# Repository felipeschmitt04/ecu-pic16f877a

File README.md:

# ECU with PIC16F877A

Academic embedded systems project developed for a **Microprocessors and
Microcontrollers** course in the Computer Engineering program at UFSC. The goal
was to build an educational ECU prototype that simulates basic combustion engine
control while integrating embedded firmware, sensor acquisition, actuator
control, an LCD interface, circuit simulation, and PCB design.

> **Disclaimer:** this project is intended for academic and portfolio purposes.
> It has not been validated for real automotive use and must not be used to
> control an actual engine without proper electrical, mechanical, and safety
> reviews.

## Overview

The ECU firmware was written in C for the **PIC16F877A** microcontroller using
MPLAB X and the XC8 compiler. The system reads simulated analog sensors, applies
fuel injection maps, controls injectors, ignition outputs, auxiliary actuators,
and displays runtime data on a 16x2 LCD.

The project includes:

- Proteus circuit simulation;
- KiCad schematic and PCB design;
- economy and performance injection maps;
- active map persistence using internal EEPROM;
- button-based user interface with LCD feedback;
- timer and interrupt-driven control logic.

## Visual Documentation

The repository includes exported hardware views that document the path from the
electrical design to the final PCB layout.

The schematic centers on the PIC16F877A and shows the simulated sensor inputs,
LCD interface, user buttons, power connections, and MOSFET-based output stages
used to represent injectors, ignition pairs, the fuel pump, radiator fan,
starter motor, and warning indicators.

The PCB layout shows the two-layer board routing, with the LCD and user controls
placed on the front side and the sensor/actuator connectors distributed around
the board edges for easier access during testing.

| Front side | Back side |
| --- | --- |
|  |  |

The 3D renders highlight the intended physical organization of the prototype:
LCD and buttons on the user-facing side, and the microcontroller, connectors,
crystal oscillator, potentiometer, and driver stages on the opposite side.

## Features

- ADC reading for simulated sensors:
  - TPS;
  - RPM;
  - lambda/oxygen sensor;
  - temperature.
- Two injection maps:
  - economy;
  - performance.
- Sequential injector control.
- Paired ignition output control.
- Auxiliary actuator control:
  - fuel pump;
  - radiator fan;
  - starter motor;
  - check engine LED.
- Simulated open-loop and closed-loop modes.
- RPM limiter.
- Start enrichment logic.
- Multi-screen 16x2 LCD interface.

## How the ECU Works

The firmware runs a simple ECU control loop around four simulated analog
signals: throttle position, RPM, lambda/oxygen feedback, and temperature. Each
loop iteration reads the sensors through the PIC ADC, updates the engine state,
selects a fuel value from a 16x16 lookup table, applies correction rules, and
updates the auxiliary actuators and LCD.

The fuel maps use RPM and TPS as axes. The 10-bit ADC readings are compressed
to 4-bit indexes, producing 16 RPM bands and 16 throttle bands:

```c
rpm_index = adc_rpm >> 6;
tps_index = adc_tps >> 6;
map_index = rpm_index * 16 + tps_index;
```

Two maps are available: an economy map with lower base injection values and a
performance map with richer values. The selected map is stored in internal
EEPROM so the ECU can restore it after a reset.

Timer1 schedules the engine events according to the simulated RPM. On each
Timer1 interrupt, the firmware advances a four-step engine sequence, triggers
one ignition pair, and opens one injector. Timer2 then controls the injector
pulse width and turns all injectors off when the pulse ends.

For a deeper breakdown of the sensors, maps, correction logic, and actuator
states, see [ECU operation](docs/ecu-operation.md).

## Architecture

```mermaid
flowchart LR
    A["Simulated sensors<br/>TPS, RPM, lambda, temperature"] --> B["PIC16F877A ADC"]
    B --> C["ECU logic<br/>maps, corrections, limits"]
    C --> D["Timers and interrupts"]
    D --> E["Injectors"]
    D --> F["Ignition outputs"]
    C --> G["Auxiliary actuators<br/>pump, fan, starter"]
    C --> H["16x2 LCD"]
    I["Buttons"] --> C
    C --> J["Internal EEPROM<br/>active map"]
```

## Project Structure

```text
.
├── Software-MPLab/
│   └── ecu_final.X/        # C firmware for MPLAB X / XC8
├── Hardware-Proteus/       # Circuit simulation
├── PCB-Kicad/
│   └── ecu/                # Schematic and PCB files
└── docs/                   # Technical notes and portfolio assets
```

## Technologies

- **Language:** C
- **Microcontroller:** PIC16F877A
- **IDE/Compiler:** MPLAB X + XC8
- **Simulation:** Proteus
- **PCB Design:** KiCad
- **Interface:** 16x2 LCD in 4-bit mode

## How to Open

### Firmware

1. Open `Software-MPLab/ecu_final.X` in MPLAB X.
2. Confirm that the selected device is `PIC16F877A`.
3. Build the project with the XC8 compiler.

### Simulation

1. Open `Hardware-Proteus/ecu3.pdsprj` in Proteus.
2. Attach the `.hex` file generated by MPLAB to the simulated microcontroller,
   if required.
3. Run the simulation and vary the sensor inputs to observe the ECU behavior.

### PCB

1. Open `PCB-Kicad/ecu/ecu.kicad_pro` in KiCad.
2. Review the schematic and PCB layout.
3. Run ERC/DRC before considering any manufacturing step.

## Known Limitations

This project was developed as an academic prototype. Before any use beyond
simulation, the following areas would need additional work:

- validate the electrical sizing of inductive load drivers;
- replace floating-point calculations with integer or fixed-point arithmetic to
  reduce program memory usage;
- protect variables shared between `main` and interrupt routines;
- review LCD buffers and string formatting;
- make the build reproducible outside the original MPLAB/XC8 environment;
- run and document KiCad ERC/DRC results.

## Outcome

The project was presented for the Microprocessors and Microcontrollers course
and received the maximum grade. It demonstrates practical integration between
embedded firmware, analog/digital electronics, real-time control, circuit
simulation, and PCB design.

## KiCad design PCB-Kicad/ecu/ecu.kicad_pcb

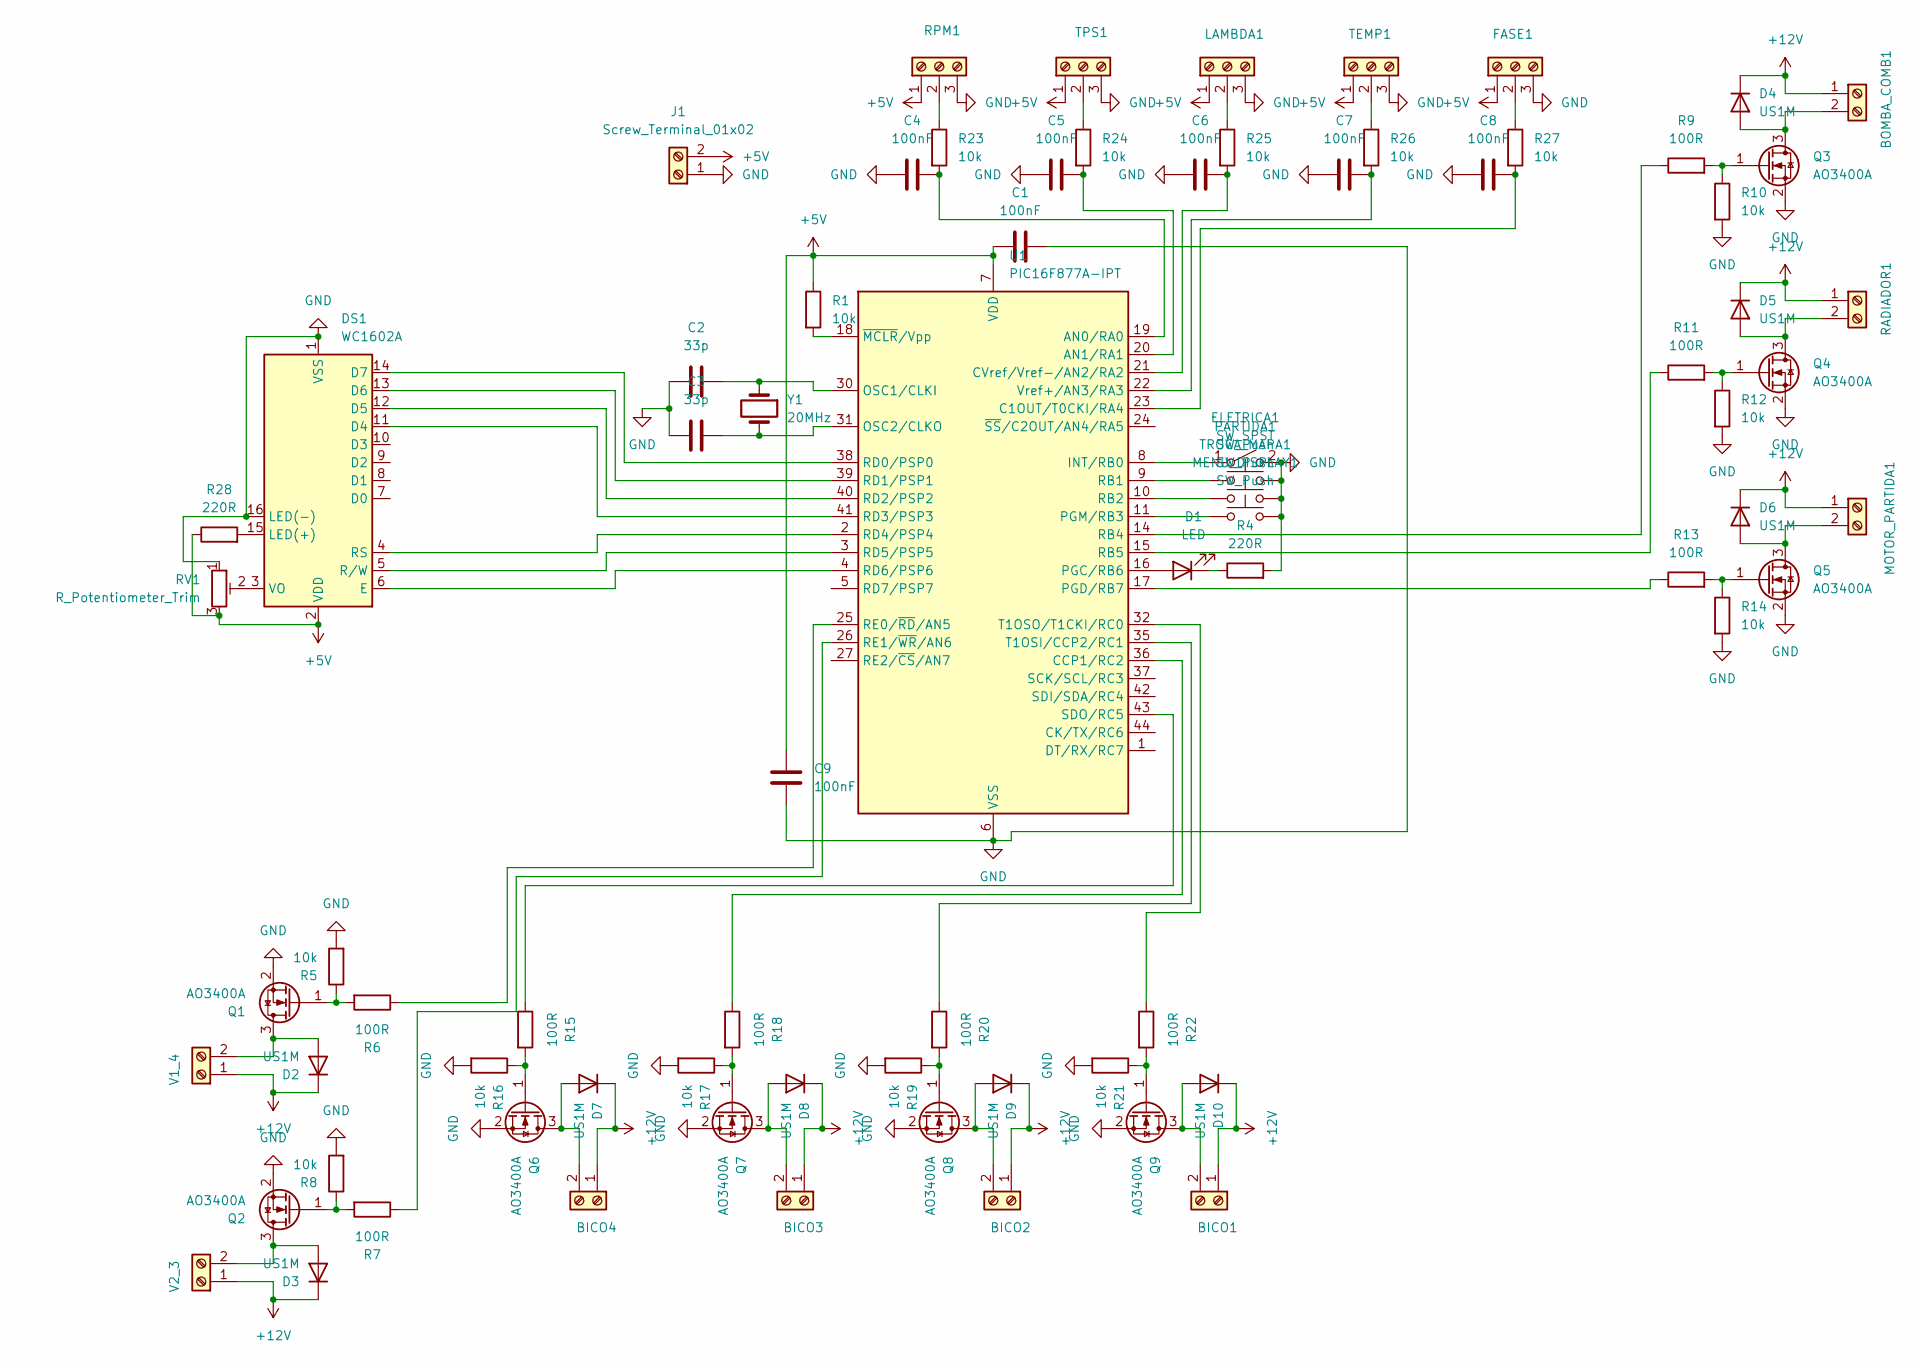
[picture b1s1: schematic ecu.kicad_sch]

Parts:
BICO1, BICO2, BICO3, BICO4: Screw_Terminal_01x02; TerminalBlock_Phoenix_PT-1,5-2-5.0-H_1x02_P5.00mm_Horizontal
BOMBA_COMB1: Screw_Terminal_01x02; TerminalBlock_Phoenix_PT-1,5-2-5.0-H_1x02_P5.00mm_Horizontal
C1, C4, C5, C6, C7, C8, C9: 100nF; C_0805_2012Metric
C2, C3: 33p; C_0805_2012Metric
D1: LED; LED_2010_5025Metric
D2, D3, D4, D5, D6, D7, D8, D9, D10: US1M; D_SMA
DS1: WC1602A
ELETRICA1: SW_SPST; SW_DIP_SPSTx01_Slide_9.78x4.72mm_W8.61mm_P2.54mm
FASE1: Screw_Terminal_01x03; TerminalBlock_Phoenix_PT-1,5-3-3.5-H_1x03_P3.50mm_Horizontal
J1: Screw_Terminal_01x02; TerminalBlock_Phoenix_MKDS-1,5-2-5.08_1x02_P5.08mm_Horizont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
LAMBDA1: Screw_Terminal_01x03; TerminalBlock_Phoenix_PT-1,5-3-3.5-H_1x03_P3.50mm_Horizontal
MENU_DISPLAY1: SW_Push; SW_Push_SPST_NO_Alps_SKRK
MOTOR_PARTIDA1: Screw_Terminal_01x02; TerminalBlock_Phoenix_PT-1,5-2-5.0-H_1x02_P5.00mm_Horizontal
PARTIDA1: SW_Push; SW_Push_SPST_NO_Alps_SKRK
Q1, Q2, Q3, Q4, Q5, Q6, Q7, Q8, Q9: AO3400A; SOT-23
R1, R5, R8, R10, R12, R14, R16, R17, R19, R21, R23, R24, R25, R26, R27: 10k; R_0805_2012Metric
R4, R28: 220R; R_0805_2012Metric
R6, R7, R9, R11, R13, R15, R18, R20, R22: 100R; R_0805_2012Metric
RADIADOR1: Screw_Terminal_01x02; TerminalBlock_Phoenix_PT-1,5-2-5.0-H_1x02_P5.00mm_Horizontal
RPM1: Screw_Terminal_01x03; TerminalBlock_Phoenix_PT-1,5-3-3.5-H_1x03_P3.50mm_Horizontal
RV1: R_Potentiometer_Trim; Potentiometer_ACP_CA6-VSMD_Vertical_Hole
TEMP1: Screw_Terminal_01x03; TerminalBlock_Phoenix_PT-1,5-3-3.5-H_1x03_P3.50mm_Horizontal
TPS1: Screw_Terminal_01x03; TerminalBlock_Phoenix_PT-1,5-3-3.5-H_1x03_P3.50mm_Horizontal
TROCA_MAPA1: SW_Push; SW_Push_SPST_NO_Alps_SKRK
U1: PIC16F877A-IPT; TQFP-44_10x10mm_P0.8mm
V1_4, V2_3: Screw_Terminal_01x02; TerminalBlock_Phoenix_PT-1,5-2-5.0-H_1x02_P5.00mm_Horizontal
Y1: 20MHz; Crystal_SMD_HC49-SD

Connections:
+5V: C1.1, C9.2, DS1.2 (VDD), FASE1.1, J1.2, LAMBDA1.1, R1.1, R28.1, RPM1.1, RV1.3, TEMP1.1, TPS1.1, U1.7 (VDD), U1.28 (VDD)
+12V: BICO1.1, BICO2.1, BICO3.1, BICO4.1, BOMBA_COMB1.1, D2.1 (K), D3.1 (K), D4.1 (K), D5.1 (K), D6.1 (K), D7.1 (K), D8.1 (K), D9.1 (K), D10.1 (K), MOTOR_PARTIDA1.1, RADIADOR1.1, V1_4.1, V2_3.1
GND: C1.2, C2.1, C3.1, C4.1, C5.1, C6.1, C7.1, C8.1, C9.1, DS1.1 (VSS), DS1.16 (LED(-)), ELETRICA1.2 (B), FASE1.3, J1.1, LAMBDA1.3, MENU_DISPLAY1.2, PARTIDA1.2, Q1.2 (S), Q2.2 (S), Q3.2 (S), Q4.2 (S), Q5.2 (S), Q6.2 (S), Q7.2 (S), Q8.2 (S), Q9.2 (S), R4.2, R5.2, R8.2, R10.2, R12.2, R14.2, R16.2, R17.2, R19.2, R21.2, RPM1.3, RV1.1, TEMP1.3, TPS1.3, TROCA_MAPA1.2, U1.6 (VSS), U1.29 (VSS)
unnamed: BICO1.2, D10.2 (A), Q9.3 (D)
unnamed: BICO2.2, D9.2 (A), Q8.3 (D)
unnamed: BICO3.2, D8.2 (A), Q7.3 (D)
unnamed: BICO4.2, D7.2 (A), Q6.3 (D)
unnamed: BOMBA_COMB1.2, D4.2 (A), Q3.3 (D)
unnamed: D1.2 (A), U1.16 (PGC/RB6)
unnamed: D1.1 (K), R4.1
unnamed: D2.2 (A), Q1.3 (D), V1_4.2
unnamed: D3.2 (A), Q2.3 (D), V2_3.2
unnamed: D5.2 (A), Q4.3 (D), RADIADOR1.2
unnamed: D6.2 (A), MOTOR_PARTIDA1.2, Q5.3 (D)
unnamed: DS1.11 (D4), U1.41 (RD3/PSP3)
unnamed: DS1.12 (D5), U1.40 (RD2/PSP2)
unnamed: DS1.13 (D6), U1.39 (RD1/PSP1)
unnamed: DS1.14 (D7), U1.38 (RD0/PSP0)
unnamed: DS1.6 (E), U1.4 (RD6/PSP6)
unnamed: DS1.15 (LED(+)), R28.2
unnamed: DS1.4 (RS), U1.2 (RD4/PSP4)
unnamed: DS1.5 (R/W), U1.3 (RD5/PSP5)
unnamed: DS1.3 (VO), RV1.2
unnamed: ELETRICA1.1 (A), U1.8 (INT/RB0)
unnamed: FASE1.2, R27.1
unnamed: LAMBDA1.2, R25.1
unnamed: Q1.1 (G), R5.1, R6.2
unnamed: Q2.1 (G), R7.2, R8.1
unnamed: Q3.1 (G), R9.2, R10.1
unnamed: Q4.1 (G), R11.2, R12.1
unnamed: Q5.1 (G), R13.2, R14.1
unnamed: Q6.1 (G), R15.2, R16.1
unnamed: Q7.1 (G), R17.1, R18.2
unnamed: Q8.1 (G), R19.1, R20.2
unnamed: Q9.1 (G), R21.1, R22.2
unnamed: R23.1, RPM1.2
unnamed: R26.1, TEMP1.2
unnamed: R24.1, TPS1.2
unnamed: C4.2, R23.2, U1.19 (AN0/RA0)
unnamed: C5.2, R24.2, U1.20 (AN1/RA1)
unnamed: C8.2, R27.2, U1.23 (C1OUT/T0CKI/RA4)
unnamed: R18.1, U1.36 (CCP1/RC2)
unnamed: C6.2, R25.2, U1.21 (CVref/Vref-/AN2/RA2)
unnamed: C2.2, U1.30 (OSC1/CLKI), Y1.1
unnamed: C3.2, U1.31 (OSC2/CLKO), Y1.2
unnamed: R13.1, U1.17 (PGD/RB7)
unnamed: MENU_DISPLAY1.1, U1.11 (PGM/RB3)
unnamed: PARTIDA1.1, U1.9 (RB1)
unnamed: TROCA_MAPA1.1, U1.10 (RB2)
unnamed: R9.1, U1.14 (RB4)
unnamed: R11.1, U1.15 (RB5)
unnamed: R6.1, U1.25 (RE0/~RD/AN5)
unnamed: R7.1, U1.26 (RE1/~WR/AN6)
unnamed: R15.1, U1.43 (SDO/RC5)
unnamed: R20.1, U1.35 (T1OSI/CCP2/RC1)
unnamed: R22.1, U1.32 (T1OSO/T1CKI/RC0)
unnamed: C7.2, R26.2, U1.22 (Vref+/AN3/RA3)
unnamed: R1.2, U1.18 (~MCLR/Vpp)

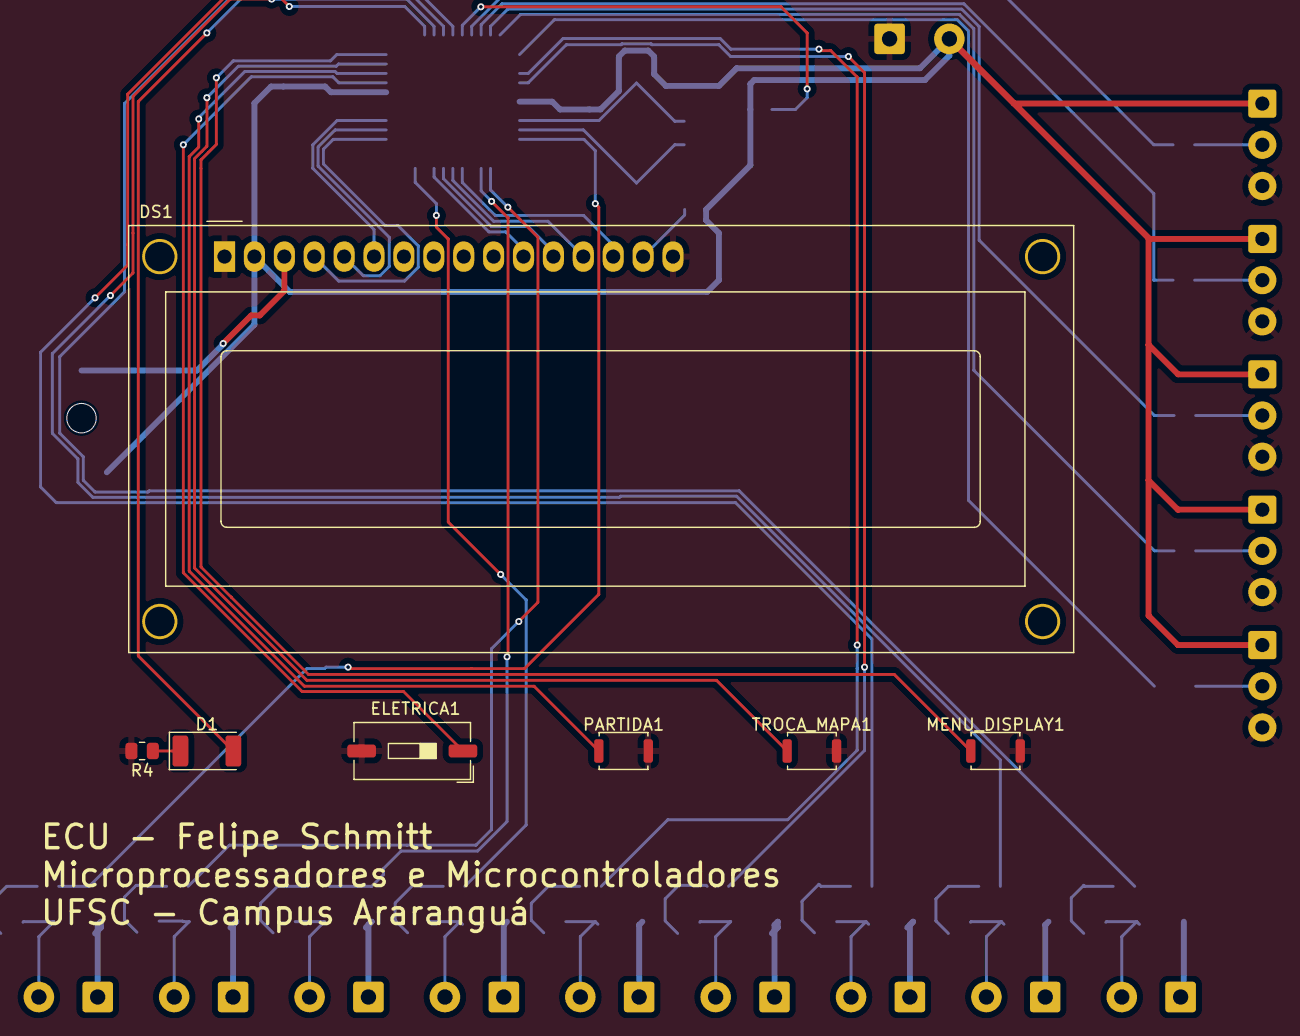
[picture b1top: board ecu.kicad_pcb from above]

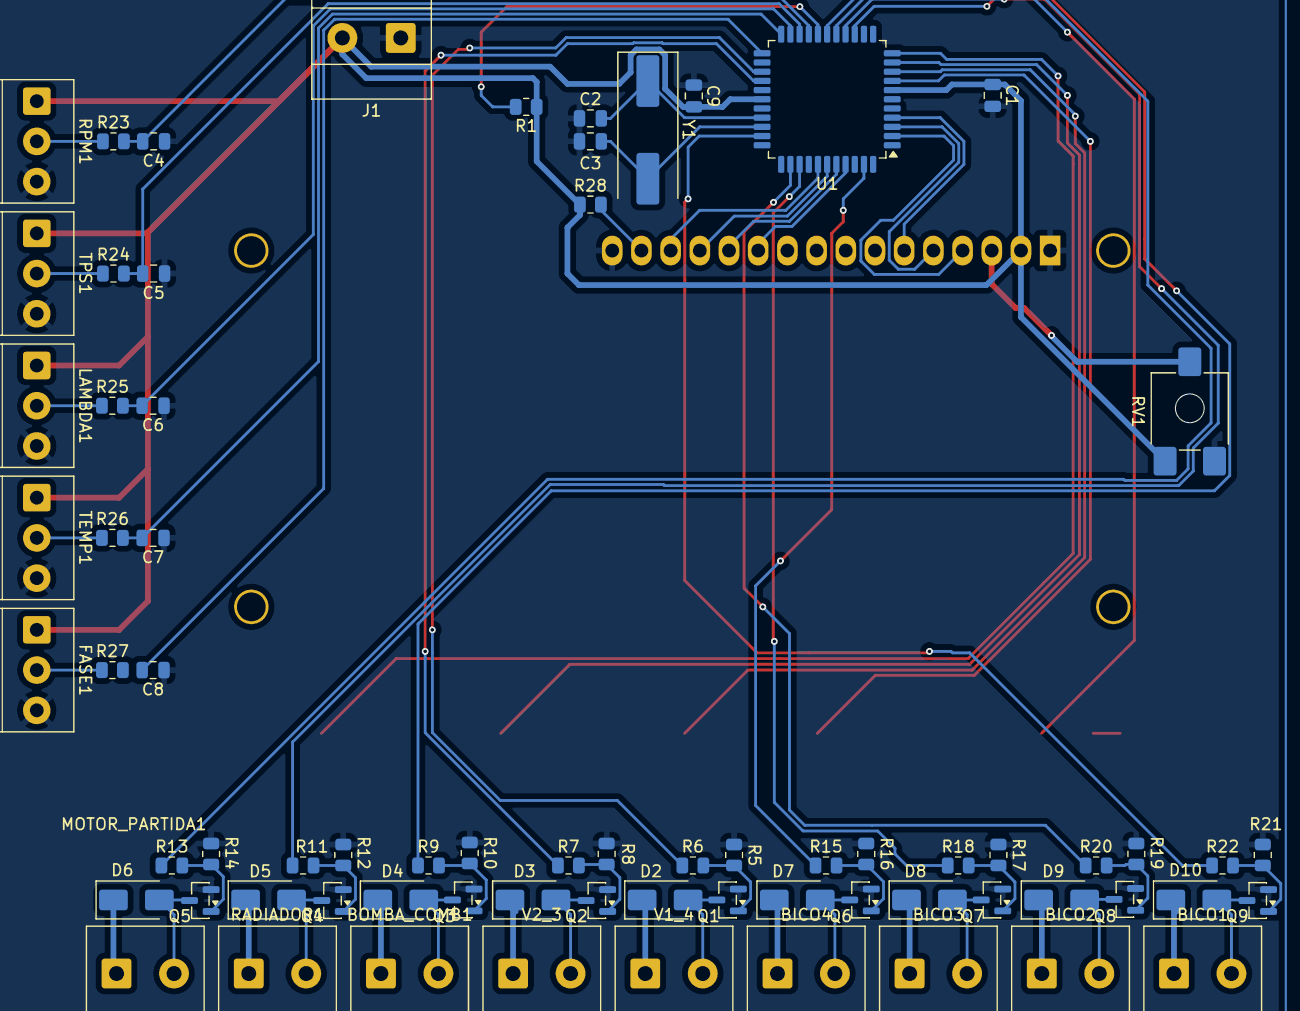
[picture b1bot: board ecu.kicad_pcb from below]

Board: 2 copper layers, 77 parts (70 on the bottom side), 58 nets.

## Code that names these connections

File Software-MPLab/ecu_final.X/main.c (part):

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/*
 * PINOS DA LCD.H
 */
#define D4 PORTDbits.RD0
#define D5 PORTDbits.RD1
#define D6 PORTDbits.RD2
#define D7 PORTDbits.RD3
#define RS PORTDbits.RD4
#define EN PORTDbits.RD6

/*
 * PINOS DO PIC
 */
//PORTA
#define FASE PORTAbits.RA4

//PORTB (entradas)
#define SW_IGNICAO PORTBbits.RB0
#define SW_PARTIDA PORTBbits.RB1
#define SW_MAPA PORTBbits.RB2
#define SW_MENU PORTBbits.RB3

//PORTB (saidas)
#define BOMBA_COMB PORTBbits.RB4
#define RADIADOR PORTBbits.RB5
#define LED_CHECK PORTBbits.RB6
#define MOTOR_PARTIDA PORTBbits.RB7

//PORTC
#define BICO_1 PORTCbits.RC0
#define BICO_2 PORTCbits.RC1
#define BICO_3 PORTCbits.RC2
#define BICO_4 PORTCbits.RC5

//PORTE
#define VELA_1_4 PORTEbits.RE0
#define VELA_2_3 PORTEbits.RE1

// RPM MAX
#define RPM_LIMITE 6500
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 * VARIAVEIS GLOBAIS
 */
// flags de estado
volatile uint8_t g_ignicao_ligada = 0; //0 = desligado, controlado pelo RB0
volatile uint8_t g_motor_girando = 0; //1 = RPM > 500
volatile uint8_t g_modo_partida = 0; // 1 = botao de partida pressionado

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    
    INTCONbits.GIE = 1; // interrupcoes globais
    INTCONbits.PEIE = 1; //interrupcoes de perifericosc
    // INTCONbits.INTE = 1; // interrupcao externa (RB0)
    
    // persistencia de dados da eeprom interna para buscar o ultimo
    // estado ativo do mapa de injeção
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
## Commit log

2026-06-18 Document academic ECU portfolio project
2026-06-18 Clean up repository naming
2026-06-18 Hide publication helper docs
2026-06-18 Translate portfolio docs to English
2026-06-18 Changed readme
2026-06-18 Document ECU runtime behavior
2026-06-19 Added images
2026-06-20 Document hardware visuals
